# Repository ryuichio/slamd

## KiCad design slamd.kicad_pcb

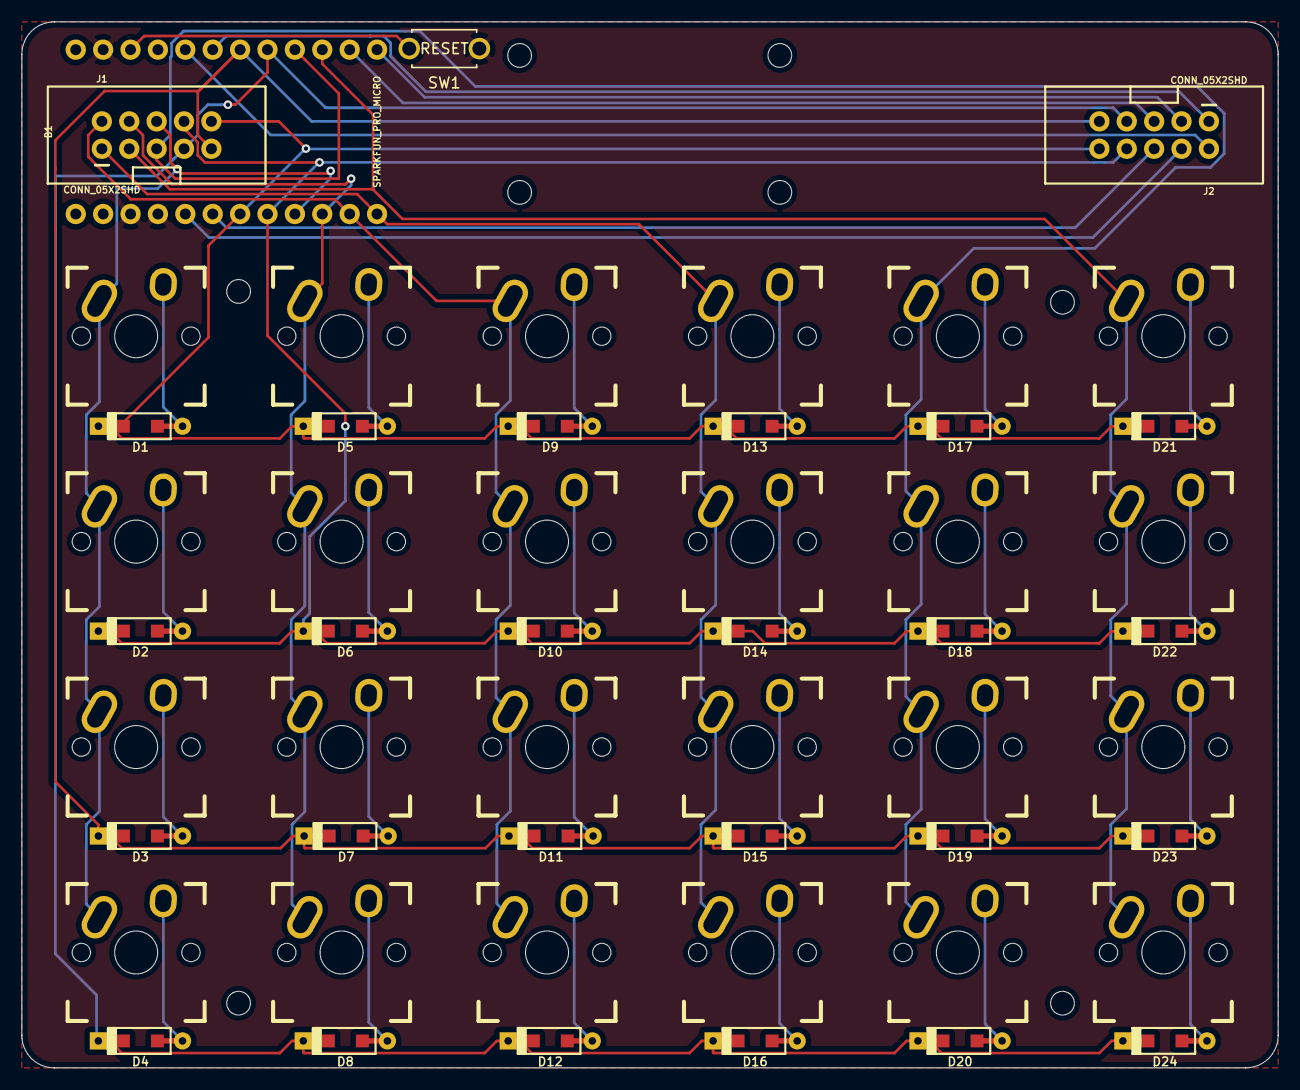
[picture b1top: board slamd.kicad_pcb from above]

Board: 2 copper layers, 116.5 x 97.0 mm, 52 parts (0 on the bottom side), 42 nets.

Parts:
B1: SPARKFUN_PRO_MICRO
D1, D2, D3, D4, D5, D6, D7, D8, D9, D10, D11, D12, D13, D14, D15, D16, D17, D18, D19, D20, D21, D22, D23, D24: D; D_SOD123_axial
J1, J2: CONN_05X2SHD; 2X5-SHROUDED
K1, K2, K3, K4, K5, K6, K7, K8, K9, K10, K11, K12, K13, K14, K15, K16, K17, K18, K19, K20, K21, K22, K23, K24: KEYSW; Mx_Alps_100
SW1: SW_PUSH; ResetSW

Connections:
/col0: B1.9, J1.6, K1.1, K2.1, K3.1, K4.1
/col1: B1.10, J1.4, K5.1, K6.1, K7.1, K8.1
/col2: B1.11, J1.2, K9.1, K10.1, K11.1, K12.1
/col3: B1.12, J1.1, K13.1, K14.1, K15.1, K16.1
/col4: B1.16, J1.5, K17.1, K18.1, K19.1, K20.1
/col5: B1.15, J1.3, K21.1, K22.1, K23.1, K24.1
/col6: B1.14, J2.5
/col7: B1.13, J2.3
/col8: B1.19, J2.1
/col9: B1.20, J2.2
/col10: B1.6, J2.6
/col11: B1.5, J2.4
/row0: B1.7, D1.1, D5.1, D9.1, D13.1, D17.1, D21.1, J1.10, J2.10
/row1: B1.8, D2.1, D6.1, D10.1, D14.1, D18.1, D22.1, J1.8, J2.8
/row2: B1.18, D3.1, D7.1, D11.1, D15.1, D19.1, D23.1, J1.9, J2.9
/row3: B1.17, D4.1, D8.1, D12.1, D16.1, D20.1, D24.1, J1.7, J2.7
/rst: B1.22, SW1.2
GND: B1.3, B1.4, B1.23, SW1.1
unnamed: D1.2, K1.2
unnamed: D2.2, K2.2
unnamed: D3.2, K3.2
unnamed: D4.2, K4.2
unnamed: D5.2, K5.2
unnamed: D6.2, K6.2
unnamed: D7.2, K7.2
unnamed: D8.2, K8.2
unnamed: D9.2, K9.2
unnamed: D10.2, K10.2
unnamed: D11.2, K11.2
unnamed: D12.2, K12.2
unnamed: D13.2, K13.2
unnamed: D14.2, K14.2
unnamed: D15.2, K15.2
unnamed: D16.2, K16.2
unnamed: D17.2, K17.2
unnamed: D18.2, K18.2
unnamed: D19.2, K19.2
unnamed: D20.2, K20.2
unnamed: D21.2, K21.2
unnamed: D22.2, K22.2
unnamed: D23.2, K23.2
unnamed: D24.2, K24.2

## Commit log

2020-02-16 modified environmets
2020-06-21 Added mouting holes
2020-06-28 turned 180 degree the left side connector
2020-06-28 add mouting holes for a protector
2020-07-04 adjust mounting holes
2020-07-04 change reset sw
2020-07-04 backup ordered files
